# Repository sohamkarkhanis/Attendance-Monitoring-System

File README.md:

# Attendance Monitoring System

This repository contains the code and documentation for an Attendance Monitoring System based on the ESP32 with a DS3231 RTC and the Hitachi HD44780, 16x2 character LCD with a PCF8574 I2C backpack. The system allows users to record attendance using a 4x4 matrix keypad through which Roll Numbers are entered and registered.

This project is designed to automate the process of attendance taking, saving time and reducing errors. With a focus on simplicity and cost-efficiency, it offers a dependable solution for monitoring the attendance in small institutions where advanced methods such as RFID, biometrics, etc… are not required.

Refer to the block diagram, PCB layout, schematic, and the code within the repository for detailed explanations and understanding of the project's functionality and hardware connections.

---

Author: Soham Karkhanis

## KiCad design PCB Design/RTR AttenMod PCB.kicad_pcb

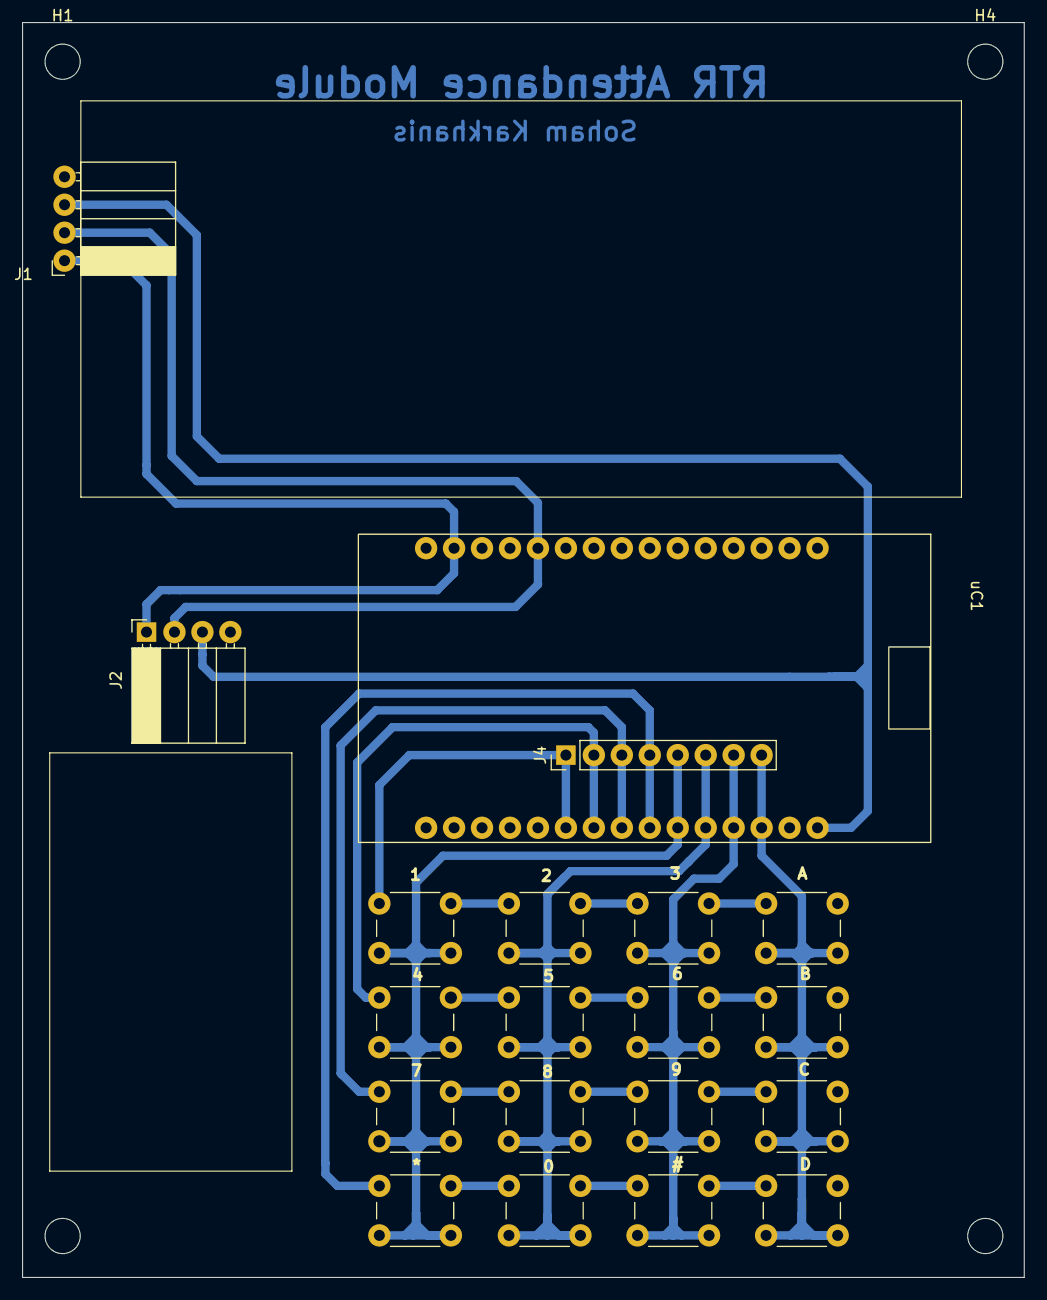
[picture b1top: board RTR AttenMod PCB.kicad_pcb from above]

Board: 2 copper layers, 91.0 x 114.0 mm, 24 parts (0 on the bottom side), 12 nets.

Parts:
H1, H2, H3, H4: MountingHole; MountingHole_3.2mm_M3
J1, J2: Conn_01x04_Male; PinSocket_1x04_P2.54mm_Horizontal
J4: Conn_01x08_Pin; PinHeader_1x08_P2.54mm_Vertical
SW1, SW2, SW3, SW4, SW5, SW6, SW7, SW8, SW9, SW10, SW11, SW12, SW13, SW14, SW15, SW16: SW_Push_45deg; SW_PUSH_6mm
uC1: ESP32_30_Pin

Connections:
/5V: J1.3, J2.3, uC1.30 (VIN)
/C1: J4.5, SW1.2, SW2.2, SW3.2, SW4.2, uC1.25 (GPIO27)
/C2: J4.6, SW5.2, SW6.2, SW7.2, SW8.2, uC1.26 (GPIO14)
/C3: J4.7, SW9.2, SW10.2, SW11.2, SW12.2, uC1.27 (GPIO12)
/C4: J4.8, SW13.2, SW14.2, SW15.2, SW16.2, uC1.28 (GPIO13)
/R1: J4.1, SW1.1, SW5.1, SW9.1, SW13.1, uC1.21 (GPIO32)
/R2: J4.2, SW2.1, SW6.1, SW10.1, SW14.1, uC1.22 (GPIO33)
/R3: J4.3, SW3.1, SW7.1, SW11.1, SW15.1, uC1.23 (GPIO25)
/R4: J4.4, SW4.1, SW8.1, SW12.1, SW16.1, uC1.24 (GPIO26)
/SCL: J1.1, J2.1, uC1.14 (I2C SCL)
/SDA: J1.2, J2.2, uC1.11 (I2C SDA)
GND: J1.4, J2.4, uC1.2 (GND), uC1.29 (GND)

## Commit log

2023-05-21 Init
